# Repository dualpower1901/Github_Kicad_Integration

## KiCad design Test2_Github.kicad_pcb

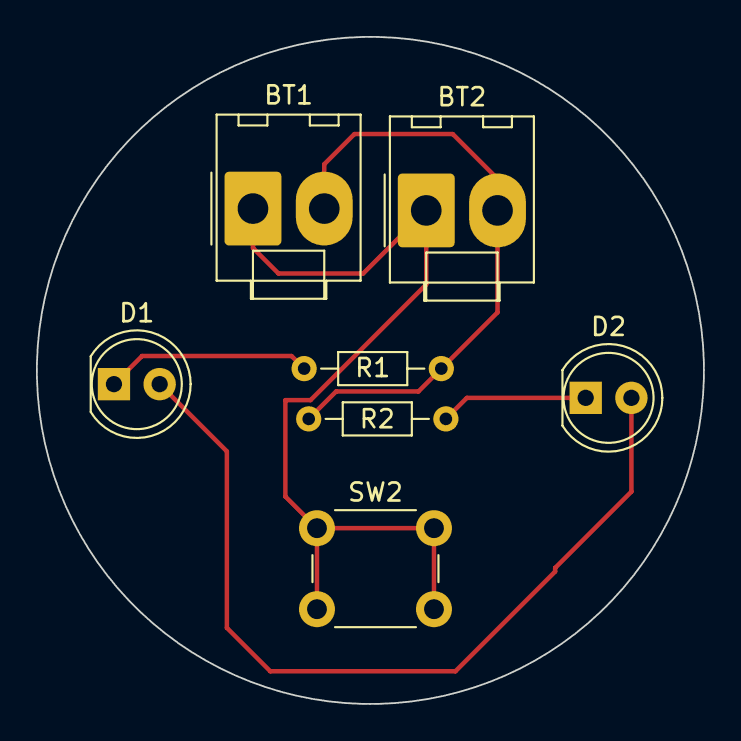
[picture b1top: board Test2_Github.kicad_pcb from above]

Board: 2 copper layers, 37.1 x 37.1 mm, 7 parts (0 on the bottom side), 5 nets.

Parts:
BT1, BT2: Battery_Cell; Molex_KK-396_A-41791-0002_1x02_P3.96mm_Vertical
D1, D2: LED; LED_D5.0mm_Clear
R1, R2: R_US; R_Axial_DIN0204_L3.6mm_D1.6mm_P7.62mm_Horizontal
SW2: SW_MEC_5E; SW_PUSH_6mm

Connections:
unnamed: BT1.1 (+), BT2.1 (+), SW2.1 (A), SW2.2 (K)
unnamed: BT1.2 (-), BT2.2 (-), R1.2, R2.2
unnamed: D1.2 (A), D2.2 (A)
unnamed: D1.1 (K), R1.1
unnamed: D2.1 (K), R2.1

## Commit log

2024-03-02 Intial commit
2024-03-02 Schematic added
2024-03-02 THT Footprint assigned
2024-03-02 Push button symbol changed
2024-03-02 symbol edit the pin number as per footprint
2024-03-02 component placement is done
2024-03-02 Routing done
